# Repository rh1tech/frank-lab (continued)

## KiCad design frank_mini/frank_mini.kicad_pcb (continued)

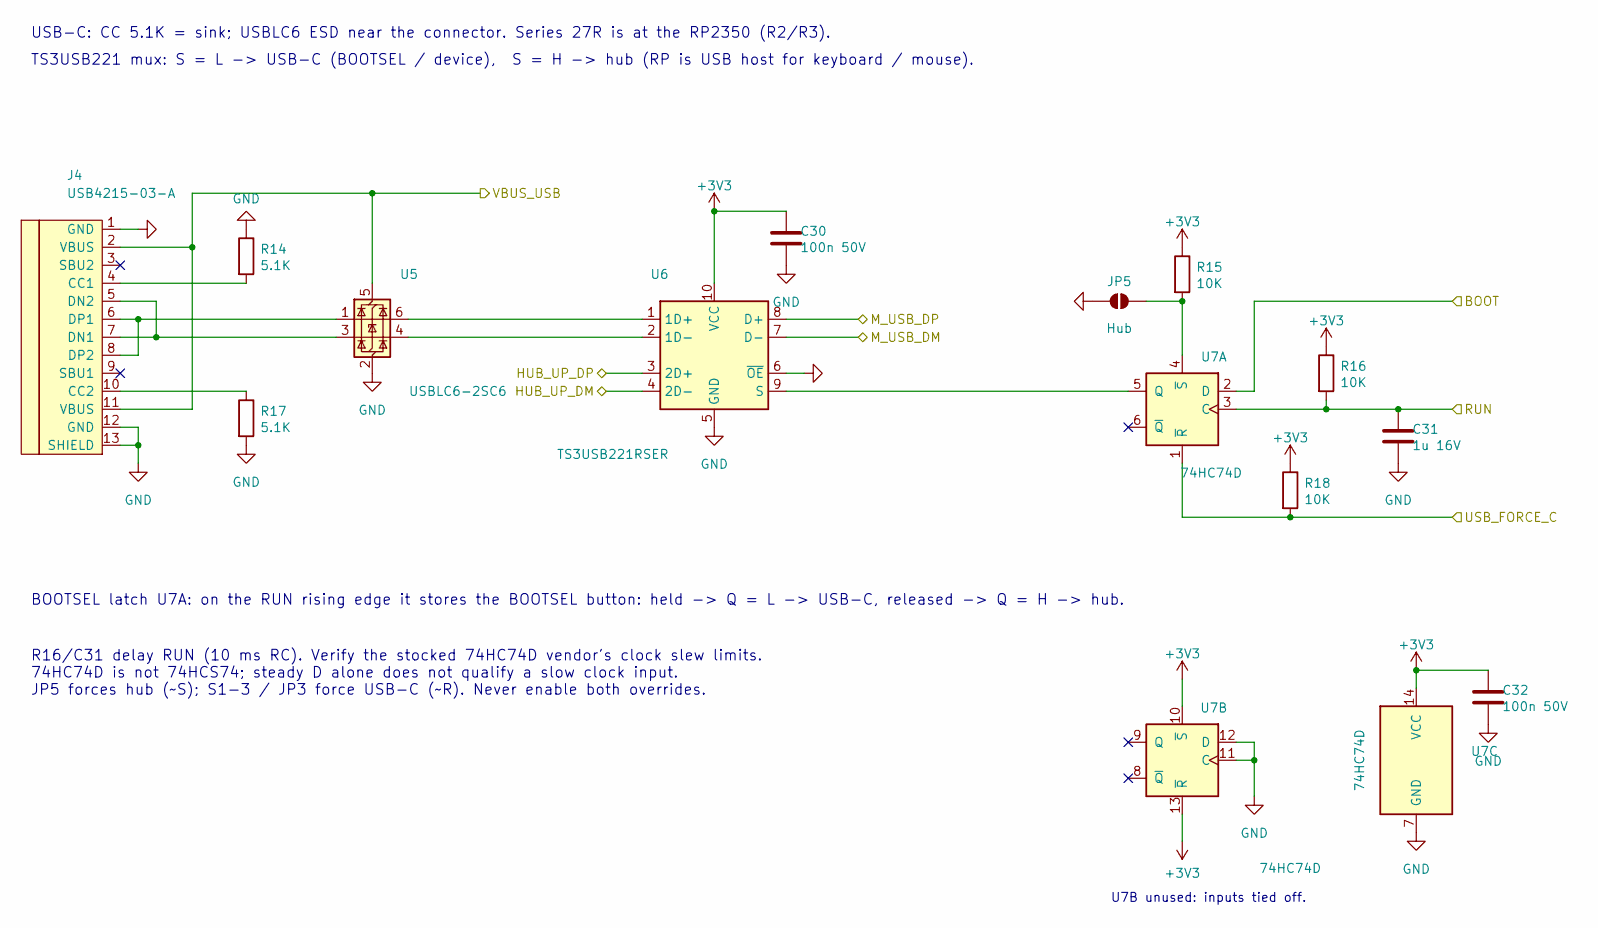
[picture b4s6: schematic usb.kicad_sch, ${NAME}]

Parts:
C30, C32: 100n 50V; C_0603_1608Metric
C31: 1u 16V; C_0603_1608Metric
J4: USB4215-03-A; USB_C_Receptacle; LCSC C165948
JP5: Hub; SolderJumper-2_P1.3mm_Open_RoundedPad1.0x1.5mm
R14, R17: 5.1K; R_0603_1608Metric
R15, R16, R18: 10K; R_0603_1608Metric
U5: USBLC6-2SC6; SOT-23-6
U6: TS3USB221RSER; UQFN-10
U7: 74HC74D; SOIC-14_P1.27mm

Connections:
+3V3: C30.1, C32.1, R15.1, R16.1, R18.1, U6.10 (VCC), U7.10 (~S), U7.13 (~R), U7.14 (VCC); also elsewhere on the board
/HUB_UP_DM: U6.4 (2D-); also elsewhere on the board
/HUB_UP_DP: U6.3 (2D+); also elsewhere on the board
/M_BOOT: U7.2 (D); also elsewhere on the board
/M_RUN: C31.1, R16.2, U7.3 (C); also elsewhere on the board
/M_USB_DM: U6.7 (D-); also elsewhere on the board
/M_USB_DP: U6.8 (D+); also elsewhere on the board
/USB_FORCE_C: R18.2, U7.1 (~R); also elsewhere on the board
/VBUS_USB: J4.2 (VBUS), J4.11 (VBUS), U5.5 (VBUS); also elsewhere on the board
GND: C30.2, C31.2, C32.2, J4.1 (GND), J4.12 (GND), J4.13 (SHIELD), JP5.1 (A), R14.1, R17.2, U5.2 (GND), U6.5 (GND), U6.6 (~OE), U7.7 (GND), U7.11 (C), U7.12 (D); also elsewhere on the board
unnamed: J4.4 (CC1), R14.2
unnamed: J4.10 (CC2), R17.1
unnamed: J4.5 (DN2), J4.7 (DN1), U5.3 (I/O2)
unnamed: J4.6 (DP1), J4.8 (DP2), U5.1 (I/O1)
unnamed: JP5.2 (B), R15.2, U7.4 (~S)
unnamed: U5.6 (I/O1), U6.1 (1D+)
unnamed: U5.4 (I/O2), U6.2 (1D-)
unnamed: U6.9 (S), U7.5 (Q)

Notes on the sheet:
U7B unused: inputs tied off.
USB-C: CC 5.1K = sink; USBLC6 ESD near the connector. Series 27R is at the RP2350 (R2/R3).
BOOTSEL latch U7A: on the RUN rising edge it stores the BOOTSEL button: held -> Q = L -> USB-C, released -> Q = H -> hub.
R16/C31 delay RUN (10 ms RC). Verify the stocked 74HC74D vendor's clock slew limits. 74HC74D is not 74HCS74; steady D alone does not qualify a slow clock input. JP5 forces hub (~S); S1-3 / JP3 force USB-C (~R). Never enable both overrides.
TS3USB221 mux: S = L -> USB-C (BOOTSEL / device), S = H -> hub (RP is USB host for keyboard / mouse).

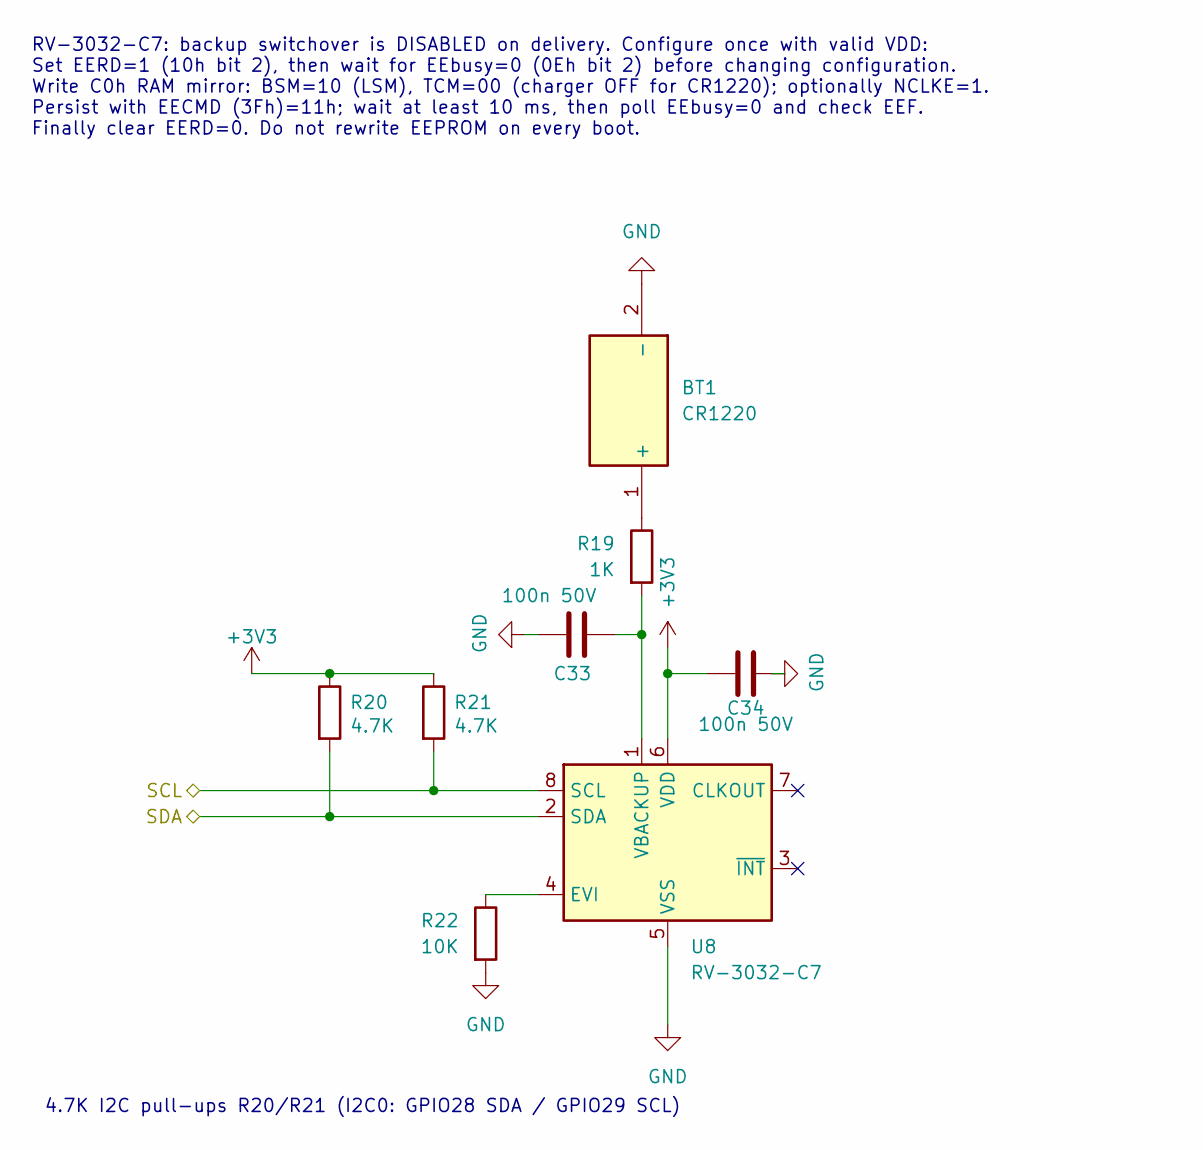
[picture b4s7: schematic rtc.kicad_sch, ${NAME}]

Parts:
BT1: CR1220; Battery_CR1220_MYOUNG_BS-12-B3AA003; Manufacturer_Part_Number BS-12-B3AA003; LCSC C964723
C33, C34: 100n 50V; C_0603_1608Metric; LCSC C14663
R19: 1K; R_0603_1608Metric; LCSC C21190
R20, R21: 4.7K; R_0603_1608Metric
R22: 10K; R_0603_1608Metric; LCSC C2906982
U8: RV-3032-C7; LCSC C5127802

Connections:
+3V3: C34.1, R20.1, R21.1, U8.6 (VDD); also elsewhere on the board
/M28_RT_SDA: R20.2, U8.2 (SDA); also elsewhere on the board
/M29_RT_SCL: R21.2, U8.8 (SCL); also elsewhere on the board
GND: BT1.2 (-), C33.1, C34.2, R22.2, U8.5 (VSS); also elsewhere on the board
unnamed: BT1.1 (+), R19.1
unnamed: R22.1, U8.4 (EVI)
unnamed: C33.2, R19.2, U8.1 (VBACKUP)

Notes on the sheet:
RV-3032-C7: backup switchover is DISABLED on delivery. Configure once with valid VDD: Set EERD=1 (10h bit 2), then wait for EEbusy=0 (0Eh bit 2) before changing configuration. Write C0h RAM mirror: BSM=10 (LSM), TCM=00 (charger OFF for CR1220); optionally NCLKE=1. Persist with EECMD (3Fh)=11h; wait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
4.7K I2C pull-ups R20/R21 (I2C0: GPIO28 SDA / GPIO29 SCL)

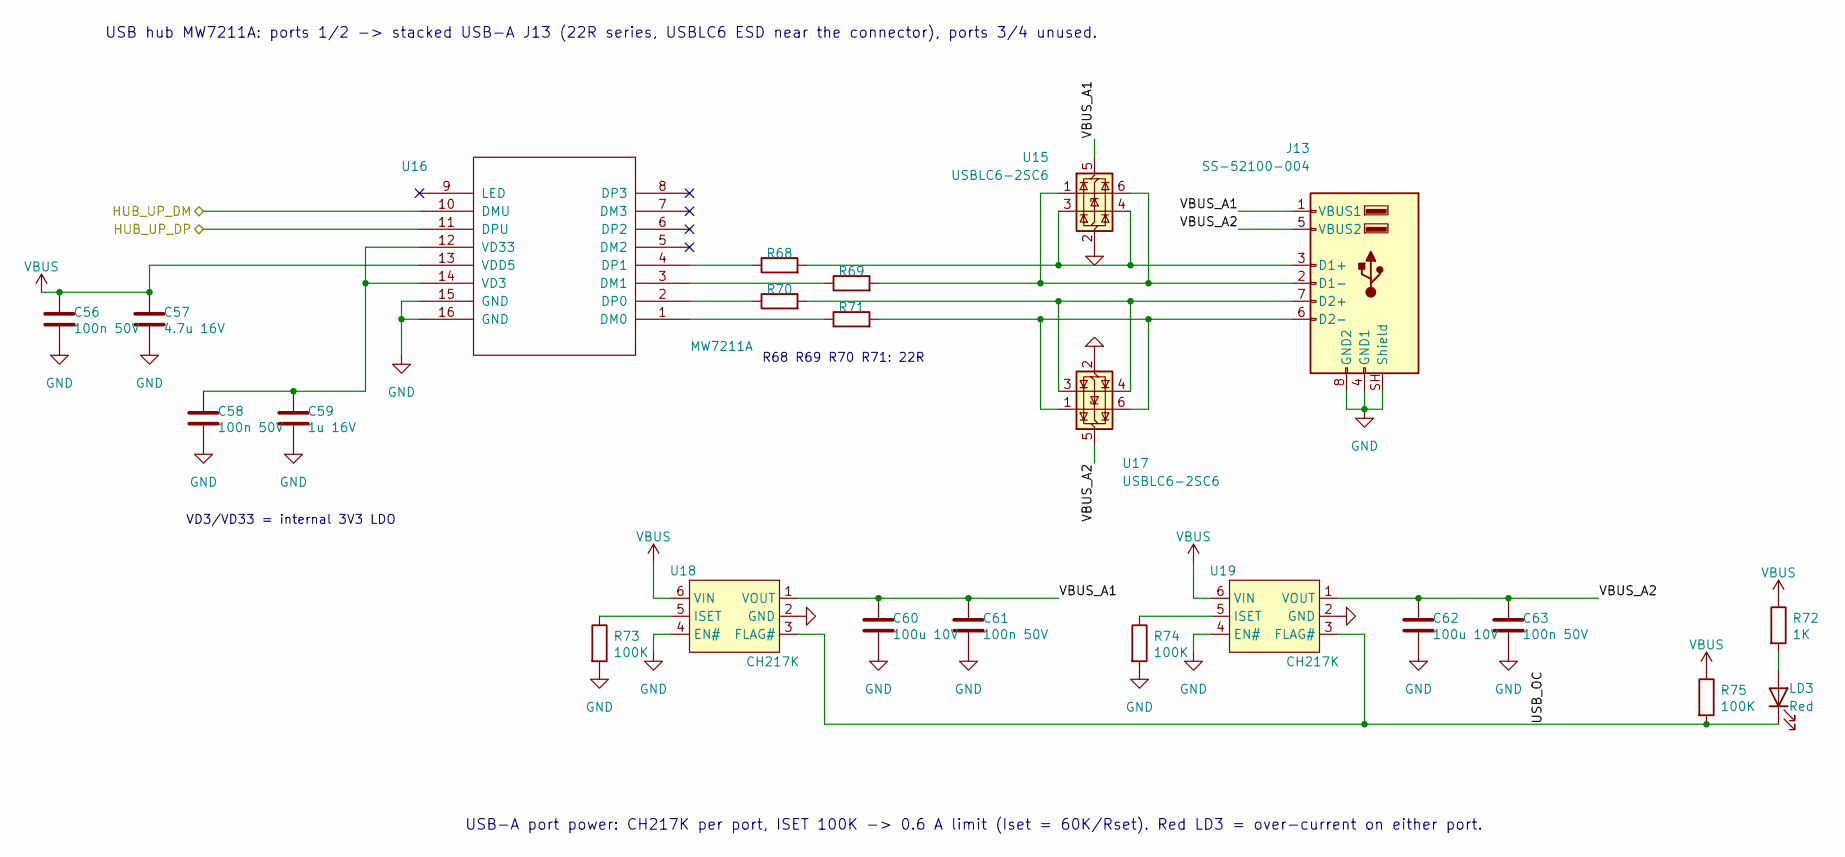
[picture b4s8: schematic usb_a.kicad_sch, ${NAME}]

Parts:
C56, C58, C61, C63: 100n 50V; C_0603_1608Metric
C57: 4.7u 16V; C_0603_1608Metric
C59: 1u 16V; C_0603_1608Metric
C60, C62: 100u 10V; C_1206_3216Metric
J13: SS-52100-004; USB_A_Stacked
LD3: Red; LED_0603_1608Metric
R68, R69, R70, R71: 22R; R_0603_1608Metric
R72: 1K; R_0603_1608Metric
R73, R74, R75: 100K; R_0603_1608Metric
U15, U17: USBLC6-2SC6; SOT-23-6
U16: MW7211A; SOP-16
U18, U19: CH217K; SOT-23-6

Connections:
/HUB_UP_DM: U16.10 (DMU); also elsewhere on the board
/HUB_UP_DP: U16.11 (DPU); also elsewhere on the board
/USB-A/USB_OC: LD3.1 (K), R75.2, U18.3 (FLAG#), U19.3 (FLAG#)
/USB-A/VBUS_A1: C60.1, C61.1, J13.1 (VBUS1), U15.5 (VBUS), U18.1 (VOUT)
/USB-A/VBUS_A2: C62.1, C63.1, J13.5 (VBUS2), U17.5 (VBUS), U19.1 (VOUT)
GND: C56.2, C57.2, C58.2, C59.2, C60.2, C61.2, C62.2, C63.2, J13.4 (GND1), J13.8 (GND2), J13.SH (Shield), R73.2, R74.2, U15.2 (GND), U16.15 (GND), U16.16 (GND), U17.2 (GND), U18.2 (GND), U18.4 (EN#), U19.2 (GND), U19.4 (EN#); also elsewhere on the board
unnamed: J13.3 (D1+), R68.2, U15.3 (I/O2), U15.4 (I/O2)
unnamed: J13.2 (D1-), R69.2, U15.1 (I/O1), U15.6 (I/O1)
unnamed: J13.7 (D2+), R70.2, U17.3 (I/O2), U17.4 (I/O2)
unnamed: J13.6 (D2-), R71.2, U17.1 (I/O1), U17.6 (I/O1)
unnamed: LD3.2 (A), R72.2
unnamed: R71.1, U16.1 (DM0)
unnamed: R69.1, U16.3 (DM1)
unnamed: R70.1, U16.2 (DP0)
unnamed: R68.1, U16.4 (DP1)
unnamed: C58.1, C59.1, U16.12 (VD33), U16.14 (VD3)
unnamed: R73.1, U18.5 (ISET)
unnamed: R74.1, U19.5 (ISET)
VBUS: C56.1, C57.1, R72.1, R75.1, U16.13 (VDD5), U18.6 (VIN), U19.6 (VIN); also elsewhere on the board

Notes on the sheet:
USB hub MW7211A: ports 1/2 -> stacked USB-A J13 (22R series, USBLC6 ESD near the connector), ports 3/4 unused.
VD3/VD33 = internal 3V3 LDO
R68 R69 R70 R71: 22R
USB-A port power: CH217K per port, ISET 100K -> 0.6 A limit (Iset = 60K/Rset). Red LD3 = over-current on either port.

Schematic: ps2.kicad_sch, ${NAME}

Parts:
C50, C51, C52: 100n 50V; C_0603_1608Metric
J11: MDC-036; MiniDIN_6pin_Female
U13: TXS0104EDR; SOIC-14_P1.27mm

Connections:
+3V3: C50.1, U13.1 (VCCA), U13.8 (OE); also elsewhere on the board
/M0_PS_MCLK_TX: U13.4 (A3); also elsewhere on the board
/M1_PS_MDAT_RX: U13.5 (A4); also elsewhere on the board
/M2_PS_KCLK: U13.2 (A1); also elsewhere on the board
/M3_PS_KDAT: U13.3 (A2); also elsewhere on the board
GND: C50.2, C51.2, C52.2, J11.3, U13.7 (GND); also elsewhere on the board
unnamed: J11.5, U13.13 (B1)
unnamed: J11.1, U13.12 (B2)
unnamed: J11.6, U13.11 (B3)
unnamed: J11.2, U13.10 (B4)
VBUS: C51.1, C52.1, J11.4, U13.14 (VCCB); also elsewhere on the board

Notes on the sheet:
PS/2 keyboard + mouse on one Mini-DIN (J6): TXS0104 3V3 <-> 5V, OE tied high.
C12 VCCA, C13 VCCB at U6; C11 at the connector VBUS pin. U6 has internal 10K pull-ups on both sides.

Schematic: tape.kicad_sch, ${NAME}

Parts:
C47, C48: 100n 50V; C_0603_1608Metric
J9: PJ-320D; AudioJack_3.5mm_PJ320D_TapeIn
R54: 4.7K; R_0603_1608Metric
R55, R56: 100K; R_0603_1608Metric
U12: CD4069UBM; SOIC127P600X175-14N

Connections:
+3V3: C48.1, U12.14 (VDD); also elsewhere on the board
/TP_LOAD: U12.6 (I=*C); also elsewhere on the board
/Tape In/TAPE: C47.2, J9.T
GND: C48.2, J9.S, U12.7 (VSS), U12.9 (D14), U12.11 (E), U12.13 (F); also elsewhere on the board
unnamed: C47.1, R54.2
unnamed: R54.1, R55.2, U12.1 (A)
unnamed: R56.1, U12.3 (B)
unnamed: U12.4 (H=*B), U12.5 (C)
unnamed: R55.1, R56.2, U12.2 (G-*A)

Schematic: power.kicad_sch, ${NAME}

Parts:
C18, C21, C23, C24, C27, C28: 10u 16V; C_0603_1608Metric
C19: 1u 16V; C_0603_1608Metric
C20: 220u 10V; C_Radial_D6.3mm_P2.50mm
C22, C25: 100n 50V; C_0603_1608Metric
C26: 100u 10V; C_1206_3216Metric
C29: 22p 50V; C_0603_1608Metric
F1: 1.5A 24V; Fuse_1812_4532Metric
FB1: 600R@100MHz 2A; L_0805_2012Metric
JP4: Force On; SolderJumper-2_P1.3mm_Open_RoundedPad1.0x1.5mm
L2: 2.2u; L_Cenker_CKCS3015_HandSolder
LD2: Green; LED_0603_1608Metric
Q1, Q2: AO3401A; SOT-23-3L_AOS
R9: 100K; R_0603_1608Metric
R10: 10K; R_0603_1608Metric
R11: 1K; R_0603_1608Metric
R12: 100K 1%; R_0603_1608Metric
R13: 22K 1%; R_0603_1608Metric
S4: SK12D07VG3NS
TP1: VBUS_USB_F; TestPoint_Pad_D1.0mm
TP2: VBUS_USB; TestPoint_Pad_D1.0mm
TP3: +1V1; TestPoint_Pad_D1.0mm
TP4: +5V_BUCK; TestPoint_Pad_D1.0mm
TP5: LX; TestPoint_Pad_D1.0mm
U4: SY8089AAAC; SOT-23-5

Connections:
+1V1: TP3.1 (1_1); also elsewhere on the board
+3V3: C26.1, C27.1, C28.1, C29.1, L2.2, R11.1, R12.1; also elsewhere on the board
/Power/+5V_BUCK: C23.1, C24.1, C25.1, FB1.2, TP4.1 (1_1), U4.1 (EN), U4.4 (IN)
/Power/FB: C29.2, R12.2, R13.1, U4.5 (FB)
/Power/PWR_G: C19.2, Q1.1 (G), Q2.1 (G), R9.2, R10.1
/Power/VBUS_SW: C19.1, Q1.2 (S), Q2.2 (S), R9.1
/Power/VBUS_USB_F: C18.1, F1.2, Q1.3 (D), TP1.1 (1_1)
/VBUS_USB: F1.1, TP2.1 (1_1); also elsewhere on the board
GND: C18.2, C20.2, C21.2, C22.2, C23.2, C24.2, C25.2, C26.2, C27.2, C28.2, JP4.1 (A), LD2.1 (K), R13.2, S4.2, U4.2 (GND); also elsewhere on the board
unnamed: JP4.2 (B), R10.2, S4.1
unnamed: LD2.2 (A), R11.2
unnamed: L2.1, TP5.1 (1_1), U4.3 (LX)
VBUS: C20.1, C21.1, C22.1, FB1.1, Q2.3 (D); also elsewhere on the board

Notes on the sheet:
3V3: SY8089AAAC sync buck, Vout = 0.6 x (1 + R12/R13) = 3.33 V, C29 feed-forward.
S4 pulls PWR_G low; gate RC tau ~= (R9 || R10) x C19 = 9.1 ms. R9 returns the gates to the sources on turn-off; JP4 Force On bypasses S4. This is not a regulated current limiter; measure USB hot-plug inrush with the full load.
USB-C 5 V in: F1 polyfuse, Q1/Q2 back-to-back soft switch. Reverse blocking is OFF-state only; do not feed J1/VBUS while USB-C is connected.

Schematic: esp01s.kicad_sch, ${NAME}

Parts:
C53: 100n 50V; C_0603_1608Metric
C54: 10u 16V; C_0603_1608Metric
C55: 100u 10V; C_1206_3216Metric
R64, R65, R66, R67: 10K; R_0603_1608Metric
S5: ESP Boot; KMR_2
U14: ESP-01v090; ESP-01

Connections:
+3V3: C53.1, C54.1, C55.1, R64.1, R65.1, R66.1, R67.1, U14.7 (VCC); also elsewhere on the board
/ES_RST: R64.2, U14.5 (RST); also elsewhere on the board
/M20_ES_TX_GP: U14.8 (URXD); also elsewhere on the board
/M21_ES_RX_GP: U14.1 (UTXD); also elsewhere on the board
GND: C53.2, C54.2, C55.2, S5.1, S5.3, U14.2 (GND); also elsewhere on the board
unnamed: R65.2, U14.3 (CH_PD)
unnamed: R67.2, S5.2, S5.4, U14.6 (GPIO0)
unnamed: R66.2, U14.4 (GPIO2)

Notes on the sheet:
UART: TX = ESP UTXD -> RP GPIO21, RX = ESP URXD <- RP GPIO20 (shared with the gamepad port).
ESP-01 socket: 10K pull-ups keep EN/RST/GPIO0/GPIO2 high for normal boot; hold S5 "ESP Boot" + press ESP Reset to flash it.

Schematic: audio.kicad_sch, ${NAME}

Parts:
J7: Ext_Sound; IDC-Header_2x05_P2.54mm_Vertical
J8: PJ-320D; AudioJack_3.5mm_PJ320D_AudioOut

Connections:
+3V3: J7.10; also elsewhere on the board
/Audio Multiplexer/TS_OUT_L: J7.3; also elsewhere on the board
/Audio Multiplexer/TS_OUT_R: J7.5; also elsewhere on the board
/Audio/AMP_OUTL: J8.T; also elsewhere on the board
/Audio/AMP_OUTR: J8.R; also elsewhere on the board
/M9_AU_DATA: J7.4; also elsewhere on the board
/M10_AU_SCLK: J7.1; also elsewhere on the board
/M11_AU_LRCK: J7.2; also elsewhere on the board
GND: J7.7, J7.8, J7.9, J8.S; also elsewhere on the board
VBUS: J7.6; also elsewhere on the board

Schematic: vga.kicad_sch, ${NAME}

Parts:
J6: VGA; DSUB-15_Female
R31, R32, R33: 330R; R_0603_1608Metric
R34, R35, R36: 1K; R_0603_1608Metric
R37, R38: 100R; R_0603_1608Metric

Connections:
/M12_HV_CLK-_B0: R36.1; also elsewhere on the board
/M13_HV_CLK+_B1: R33.1; also elsewhere on the board
/M14_HV_D0-_G0: R35.1; also elsewhere on the board
/M15_HV_D0+_G1: R32.1; also elsewhere on the board
/M16_HV_D1-_R0: R34.1; also elsewhere on the board
/M17_HV_D1+_R1: R31.1; also elsewhere on the board
/M18_HV_D2-_HS: R37.2; also elsewhere on the board
/M19_HV_D2+_VS: R38.2; also elsewhere on the board
GND: J6.0, J6.5, J6.6, J6.7, J6.8, J6.10; also elsewhere on the board
unnamed: J6.1, R31.2, R34.2
unnamed: J6.2, R32.2, R35.2
unnamed: J6.3, R33.2, R36.2
unnamed: J6.13, R37.1
unnamed: J6.14, R38.1

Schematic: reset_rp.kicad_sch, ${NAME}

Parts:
S7: RP Reset; KMR_2; Mouser Part Number 611-KMR221G-LFS
S8: RP Reset; TS-1234VW

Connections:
/M_RUN: S7.2, S7.4, S8.1; also elsewhere on the board
GND: S7.1, S7.3, S8.2, S8.3 (GND); also elsewhere on the board

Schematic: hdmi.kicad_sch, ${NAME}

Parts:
C35: 100n 50V; C_0603_1608Metric
D1: 1N5819WS; D_SOD-323
J5: DC3RX19JA2; HDMI_Female
RN1, RN2: 270R; R_Array_4x0603; LCSC C1731063

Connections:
/M12_HV_CLK-_B0: RN1.4 (R4.1); also elsewhere on the board
/M13_HV_CLK+_B1: RN1.3 (R3.1); also elsewhere on the board
/M14_HV_D0-_G0: RN1.2 (R2.1); also elsewhere on the board
/M15_HV_D0+_G1: RN1.1 (R1.1); also elsewhere on the board
/M16_HV_D1-_R0: RN2.4 (R4.1); also elsewhere on the board
/M17_HV_D1+_R1: RN2.3 (R3.1); also elsewhere on the board
/M18_HV_D2-_HS: RN2.2 (R2.1); also elsewhere on the board
/M19_HV_D2+_VS: RN2.1 (R1.1); also elsewhere on the board
GND: C35.2, J5.2 (G_D2), J5.5 (G_D1), J5.8 (G_D0), J5.11 (G_CLK), J5.17 (G_DDC/CEC), J5.20 (SHIELD1), J5.21 (SHIELD2), J5.22 (SHIELD3), J5.23 (SHIELD4); also elsewhere on the board
unnamed: C35.1, D1.1 (K), J5.18 (+5V)
unnamed: J5.12 (CLKN), RN1.5 (R4.2)
unnamed: J5.10 (CLKP), RN1.6 (R3.2)
unnamed: J5.9 (D0N), RN1.7 (R2.2)
unnamed: J5.7 (D0P), RN1.8 (R1.2)
unnamed: J5.6 (D1N), RN2.5 (R4.2)
unnamed: J5.4 (D1P), RN2.6 (R3.2)
unnamed: J5.3 (D2N), RN2.7 (R2.2)
unnamed: J5.1 (D2P), RN2.8 (R1.2)
VBUS: D1.2 (A); also elsewhere on the board

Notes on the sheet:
RN1, RN2: 270R TMDS series

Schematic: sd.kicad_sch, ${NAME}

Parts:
C49: 100n 50V; C_0603_1608Metric
J10: 104031-0811; MicroSD_SMD_Long
R58, R59, R60: 10K; R_0603_1608Metric

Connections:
+3V3: C49.1, J10.4 (VDD), R58.1, R59.1, R60.1; also elsewhere on the board
/M4_SD_DAT0: J10.7 (DAT0), R58.2; also elsewhere on the board
/M5_SD_DAT3: J10.2 (DAT3/CD), R60.2; also elsewhere on the board
/M6_SD_CLK: J10.5 (CLK); also elsewhere on the board
/M7_SD_CMD: J10.3 (CMD), R59.2; also elsewhere on the board
GND: C49.2, J10.6 (VSS), J10.SH (SHIELD); also elsewhere on the board

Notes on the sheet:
10K pull-ups on CS, CMD, DAT0 (SPI); DAT1/DAT2 unused; C49 at the socket

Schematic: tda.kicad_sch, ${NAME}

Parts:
C36, C37: 10u 16V; C_0603_1608Metric
C38: 100n 50V; C_0603_1608Metric
R39: 100R; R_0603_1608Metric
R40, R41: 470R; R_0603_1608Metric
U9: TDA1387T; SO-8

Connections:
/Audio Multiplexer/TDA_L: R41.2, U9.6 (A_LEFT); also elsewhere on the board
/Audio Multiplexer/TDA_R: R40.1, U9.8 (A_RIGHT); also elsewhere on the board
/M9_AU_DATA: U9.3 (DATA); also elsewhere on the board
/M10_AU_SCLK: U9.1 (SCLK); also elsewhere on the board
/M11_AU_LRCK: U9.2 (LRCK); also elsewhere on the board
GND: C36.2, C37.2, C38.2, R40.2, R41.1, U9.4 (AGND); also elsewhere on the board
unnamed: C36.1, U9.7 (FLT)
unnamed: C37.1, C38.1, R39.1, U9.5 (VA)
VBUS: R39.2; also elsewhere on the board

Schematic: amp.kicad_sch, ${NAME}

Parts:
C39: 10u 16V; CP_EIA-3528-12_Kemet-T
C40: 100n 50V; C_0603_1608Metric
C41, C42, C43, C44, C45: 10u 16V; C_0603_1608Metric
R42, R43, R47, R49, R52: 10K; R_0603_1608Metric
R44: 100R; R_0603_1608Metric
R45, R46, R51: 20K; R_0603_1608Metric
R48, R50: 47K; R_0603_1608Metric
U10: LM358; SO-8

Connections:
/Audio Multiplexer/AMP_IN_L: C41.1, R42.1; also elsewhere on the board
/Audio Multiplexer/AMP_IN_R: C43.1, R43.1; also elsewhere on the board
/Audio/AMP_OUTL: C42.2, R46.2; also elsewhere on the board
/Audio/AMP_OUTR: C44.2, R51.2; also elsewhere on the board
GND: C39.2, C40.1, C45.1, R42.2, R43.2, R46.1, R51.1, R52.1, U10.4 (V-); also elsewhere on the board
unnamed: C41.2, R47.2
unnamed: C42.1, R48.1, U10.7
unnamed: C43.2, R49.2
unnamed: C44.1, R50.1, U10.1
unnamed: C45.2, R45.1, R52.2, U10.3 (+), U10.5 (+)
unnamed: R49.1, R50.2, U10.2 (-)
unnamed: R47.1, R48.2, U10.6 (-)
unnamed: C39.1, C40.2, R44.2, R45.2, U10.8 (V+)
VBUS: R44.1; also elsewhere on the board

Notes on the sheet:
LM358 is not rail-to-rail: R45/R52 bias at V+/3 to preserve positive output headroom. Line output only (>=10K load); not a headphone or speaker driver.

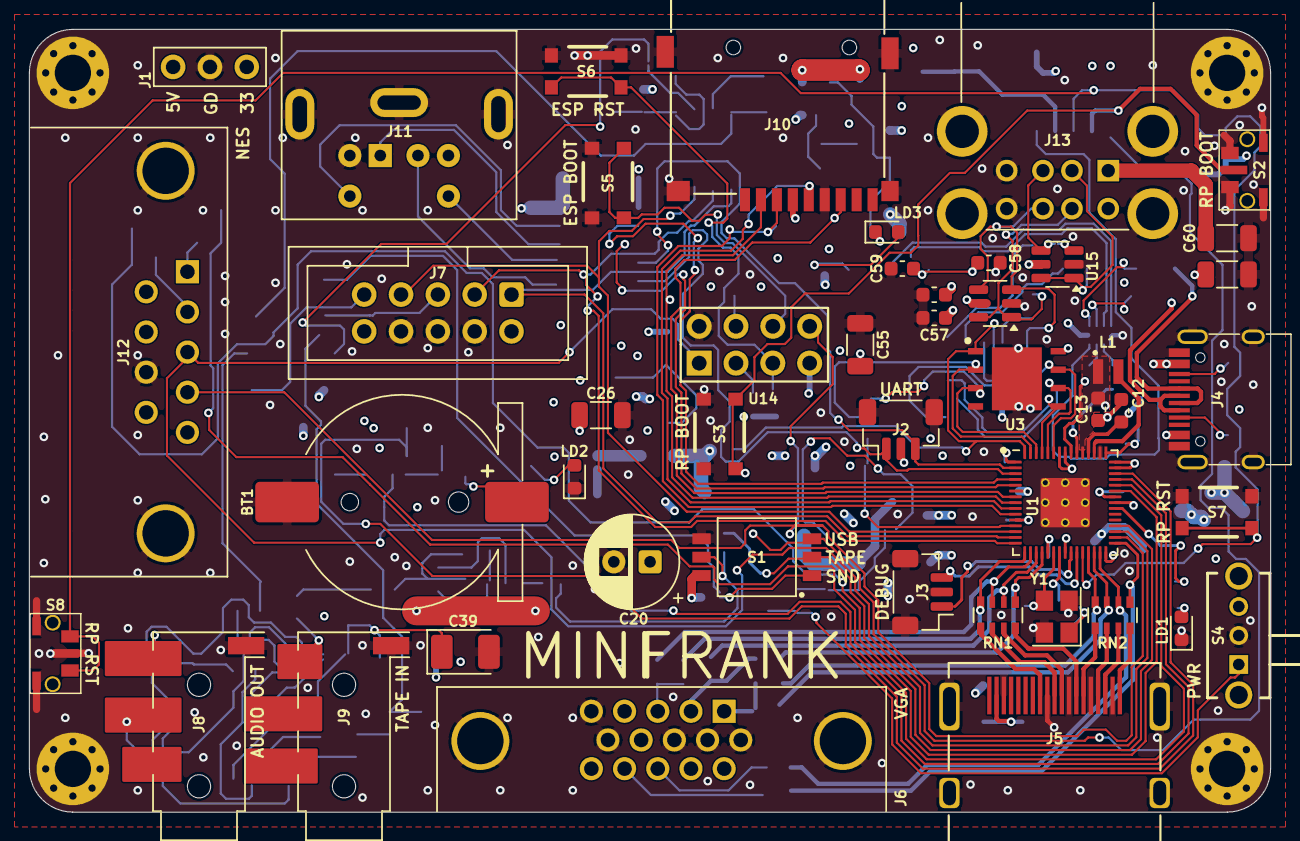
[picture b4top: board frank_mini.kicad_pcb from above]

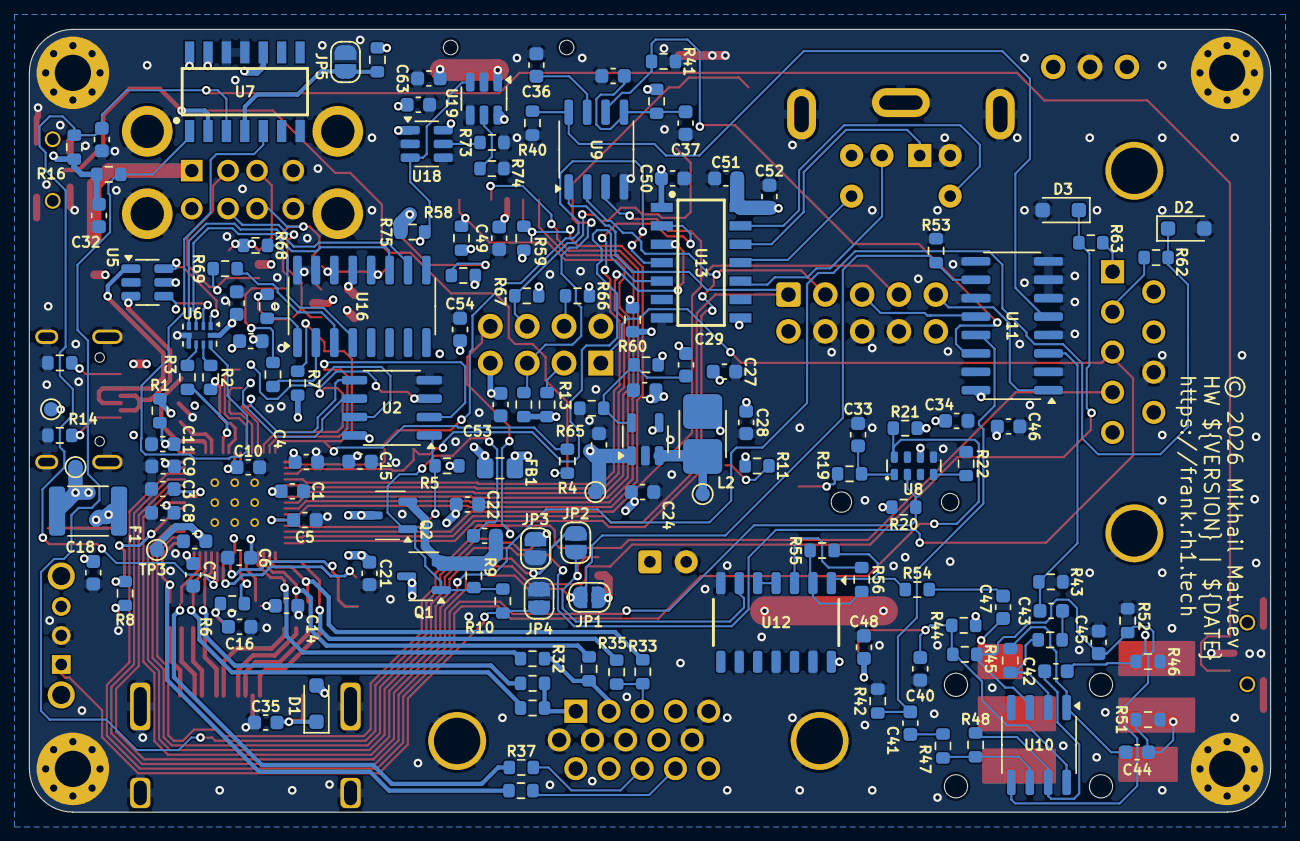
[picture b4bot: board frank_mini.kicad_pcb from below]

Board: 4 copper layers, 85.6 x 54.0 mm, 198 parts (148 on the bottom side), 140 nets.
